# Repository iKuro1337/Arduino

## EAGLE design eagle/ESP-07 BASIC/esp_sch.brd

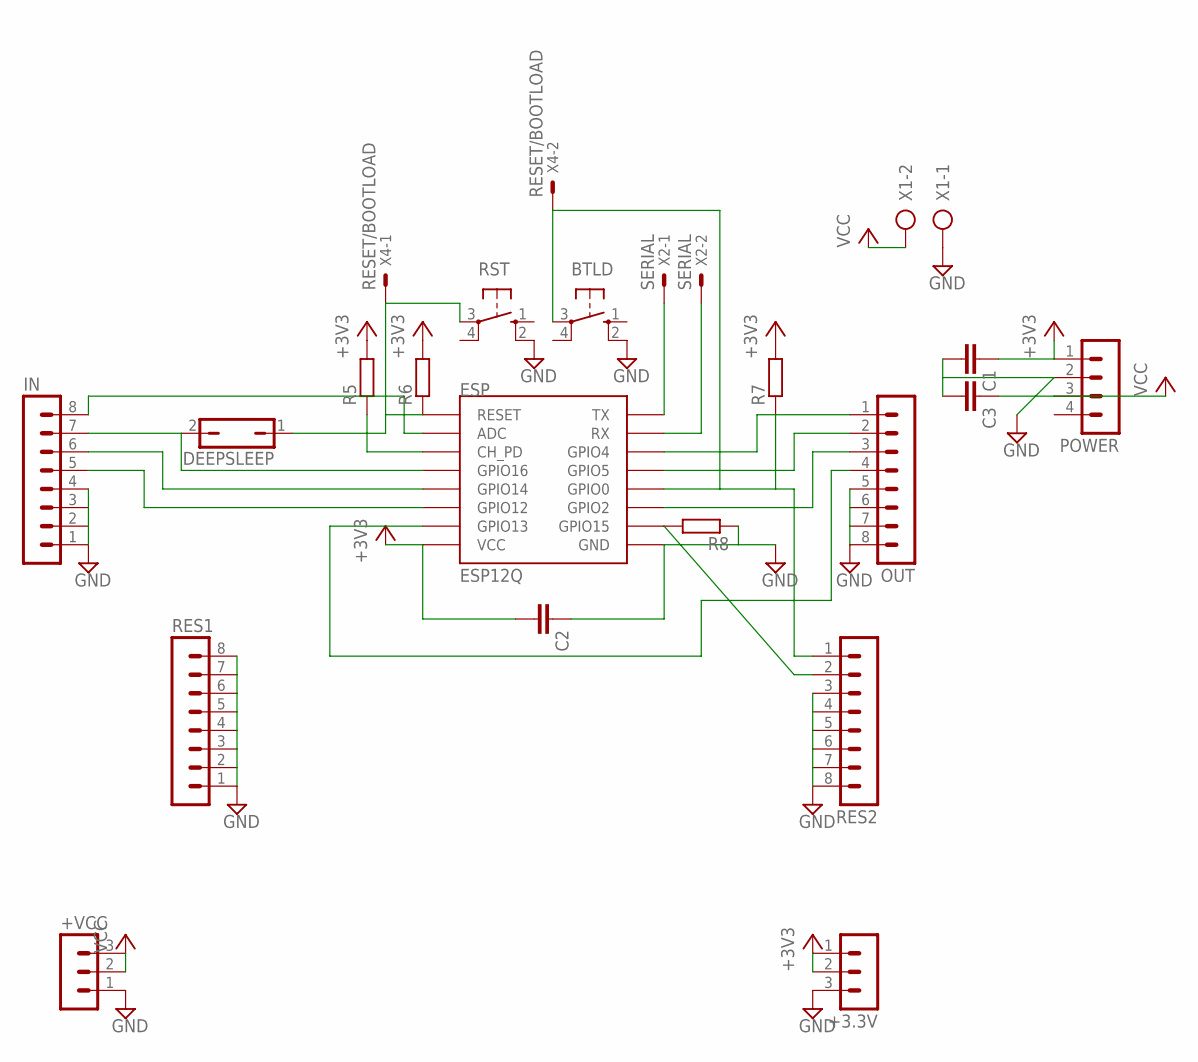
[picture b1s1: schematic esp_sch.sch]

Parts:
+3.3V: MA03-1
+VCC: MA03-1
BTLD: 10-XX; B3F-10XX
C1, C2, C3: C-EU025-024X044; C025-024X044
DEEPSLEEP: JP1Q; JP1
ESP: ESP12Q
IN: MA08-1
OUT: MA08-1
POWER: MA04-1
R5, R6, R7, R8: R; R0805
RES1, RES2: MA08-1
RST: 10-XX; B3F-10XX
X1: AK300/2
X2: SERIAL; 332-02
X4: RESET/BOOTLOAD; 332-02

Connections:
+3V3: +3.3V.1, +3.3V.2, C1.1, C2.2, ESP.VCC, POWER.1, R5.2, R6.2, R7.2
GND: +3.3V.3, +VCC.1, BTLD.2 (S1), C1.2, C2.1, C3.2, ESP.GND, IN.1, IN.2, IN.3, IN.4, OUT.5, OUT.6, OUT.7, OUT.8, POWER.2, R8.1, RES1.1, RES1.2, RES1.3, RES1.4, RES1.5, RES1.6, RES1.7, RES1.8, RES2.3, RES2.4, RES2.5, RES2.6, RES2.7, RES2.8, RST.2 (S1), X1.1
unnamed: ESP.ADC, IN.8
unnamed: BTLD.3, ESP.GPIO0, R7.1, RES2.1, X4.2
unnamed: ESP.CH_PD, R5.1
unnamed: ESP.GPIO15, R8.2, RES2.2
unnamed: ESP.TX, X2.1
unnamed: ESP.RX, X2.2
unnamed: ESP.GPIO14, IN.6
unnamed: ESP.GPIO12, IN.5
unnamed: ESP.GPIO13, OUT.4
unnamed: ESP.GPIO4, OUT.1
unnamed: ESP.GPIO5, OUT.2
unnamed: DEEPSLEEP.2, ESP.GPIO16, IN.7
unnamed: ESP.GPIO2, OUT.3
unnamed: DEEPSLEEP.1, ESP.RESET, R6.1, RST.3, X4.1
VCC: +VCC.2, +VCC.3, C3.1, POWER.3, X1.2

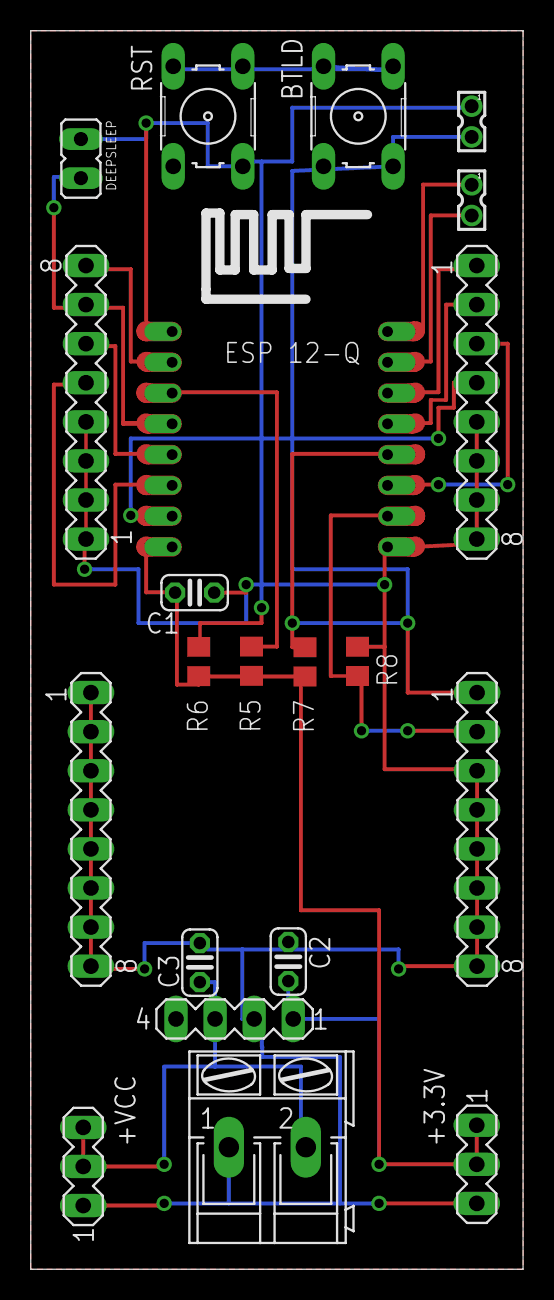
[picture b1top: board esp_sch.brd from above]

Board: 2 copper layers, 32.0 x 80.5 mm, 21 parts (0 on the bottom side), 17 nets.

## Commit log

2016-04-15 :lollipop: Added .gitattributes
2016-05-03 Added files via upload
2016-05-03 ESP8266 ARDUINO
2016-07-29 Sterownik szafowy
    Opis funkcyjny sterownika szafowego
2016-07-29 Update Sterownik
